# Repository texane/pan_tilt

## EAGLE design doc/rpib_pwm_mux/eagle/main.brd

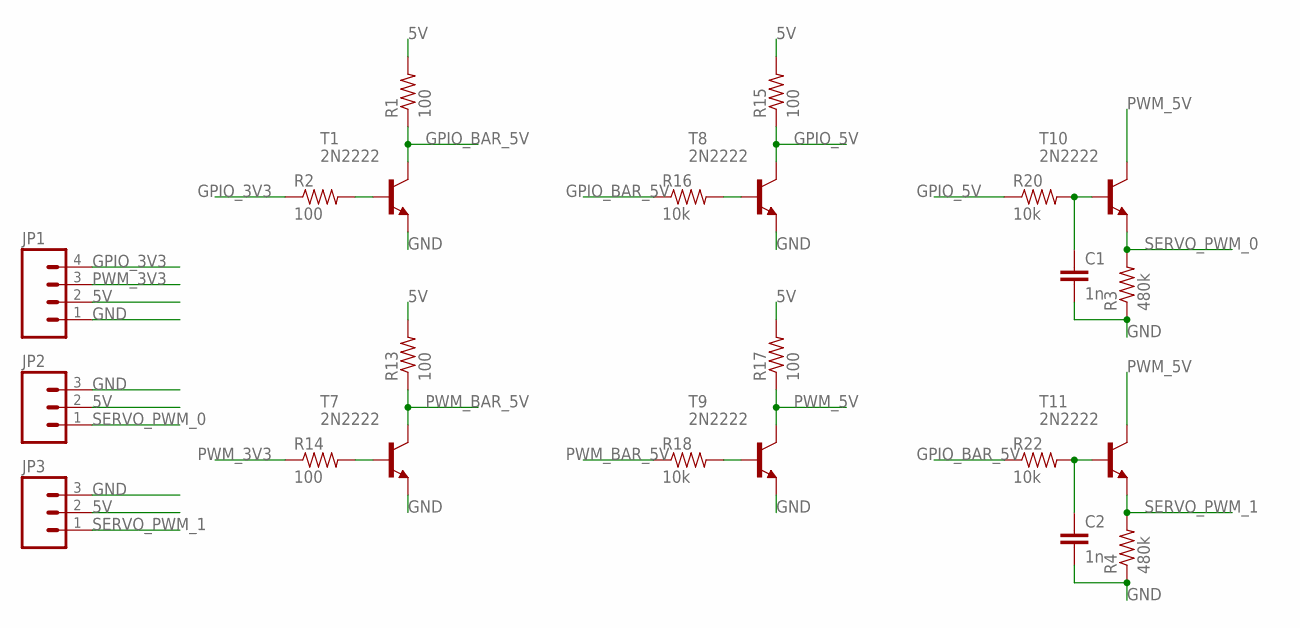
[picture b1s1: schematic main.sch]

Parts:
C1, C2: 1n; CAP-PTH-SMALL-KIT
JP1: M04LONGPADS; 1X04_LONGPADS
JP2, JP3: M03LONGPADS; 1X03_LONGPADS
R1, R2, R13, R14, R15, R17: 100; AXIAL-0.4
R3, R4: 480k; AXIAL-0.4
R16, R18, R20, R22: 10k; AXIAL-0.4
T1, T7, T8, T9, T10, T11: 2N2222; TO18

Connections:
5V: JP1.2, JP2.2, JP3.2, R1.P$2 (2), R13.P$2 (2), R15.P$2 (2), R17.P$2 (2)
GND: C1.2, C2.2, JP1.1, JP2.3, JP3.3, R3.P$1 (1), R4.P$1 (1), T1.1 (E), T7.1 (E), T8.1 (E), T9.1 (E)
GPIO_3V3: JP1.4, R2.P$1 (1)
GPIO_5V: R15.P$1 (1), R20.P$1 (1), T8.3 (C)
GPIO_BAR_5V: R1.P$1 (1), R16.P$1 (1), R22.P$1 (1), T1.3 (C)
unnamed: R2.P$2 (2), T1.2 (B)
unnamed: R14.P$2 (2), T7.2 (B)
unnamed: R16.P$2 (2), T8.2 (B)
unnamed: R18.P$2 (2), T9.2 (B)
unnamed: C1.1, R20.P$2 (2), T10.2 (B)
unnamed: C2.1, R22.P$2 (2), T11.2 (B)
PWM_3V3: JP1.3, R14.P$1 (1)
PWM_5V: R17.P$1 (1), T9.3 (C), T10.3 (C), T11.3 (C)
PWM_BAR_5V: R13.P$1 (1), R18.P$1 (1), T7.3 (C)
SERVO_PWM_0: JP2.1, R3.P$2 (2), T10.1 (E)
SERVO_PWM_1: JP3.1, R4.P$2 (2), T11.1 (E)

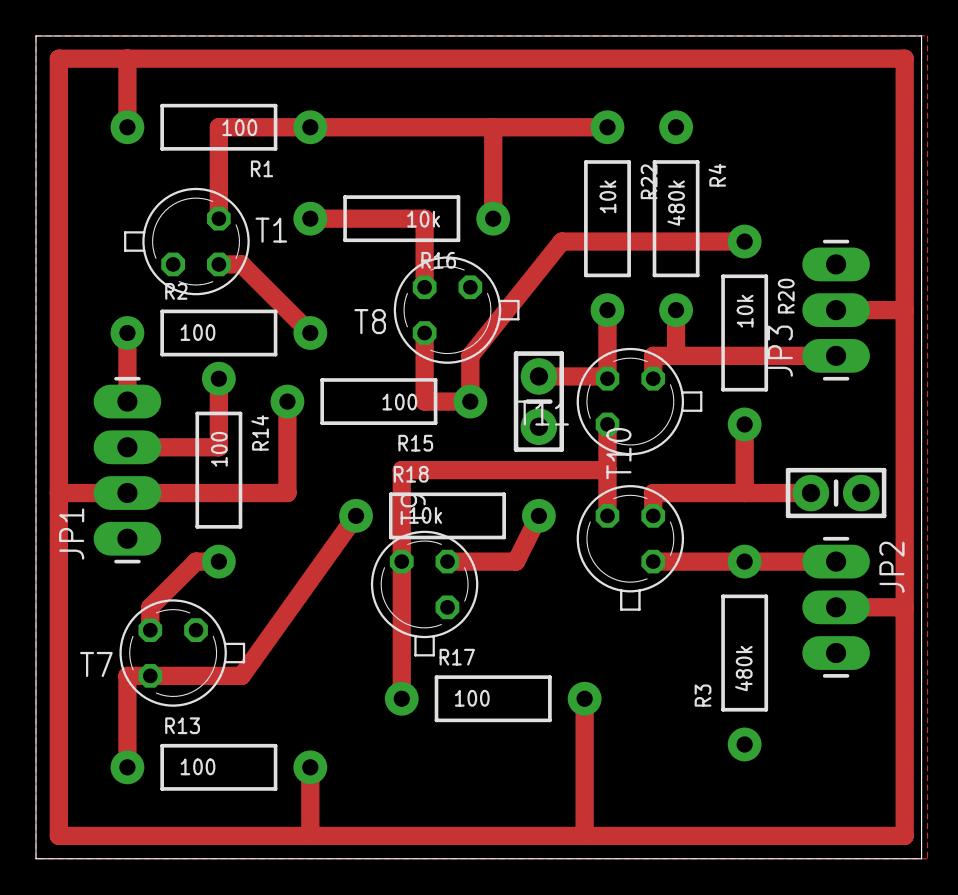
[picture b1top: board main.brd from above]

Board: 2 copper layers, 49.2 x 45.7 mm, 23 parts (0 on the bottom side), 16 nets.

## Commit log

2013-04-01 [ add ] hsr1422cr
2013-04-01 [ update ] oc2b pin
2013-04-07 [ add ] rpib_pwm_mux/eagle
2013-04-07 [ add ] rpib_pwm_mux/ltspice
2013-04-11 [ add ] src/rpib_pwm_mux
2013-04-11 [ update ] src/rpib_pwm_mux, make it compile
2013-04-12 [ add ] bcm2835-1.17
2013-04-12 [ fix ] mmap invalid argument
2013-04-13 [ update ] working pwm
2013-04-13 [ update ] pwm mode
2013-04-13 [ fix ] rpib_pwm_mux eagle
2013-04-13 [ update ] rpib_pwm_mux ltspice simulation, remove caps
2013-04-13 [ update ] rpib_pwm_mux schematics, include capa to remove spikes
2013-04-13 [ update ] rpib_pwm_mux ltspice, include capa to remove spikes
2013-04-14 [ rename ] hsr1422cr to atmega328p_hsr1422cr
2013-04-14 [ add ] src/server
2013-04-15 [ add ] src/mjpg-streamer
2013-04-15 [ add ] pantilt
2013-04-15 [ update ] move old sources in toclean directory
2013-04-15 [ fix ] pantilt, bcm2835 dirs
2013-04-15 [ add ] pics
2013-04-15 [ add ] doc/block

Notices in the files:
parts and their libraries:
SparkFun: Licensing: CC v3.0 Share-Alike You are welcome to use this library for commercial purposes.
